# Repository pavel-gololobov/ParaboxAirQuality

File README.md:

# ParaboxAirQuality
CC2538 based board for Parabox.org project

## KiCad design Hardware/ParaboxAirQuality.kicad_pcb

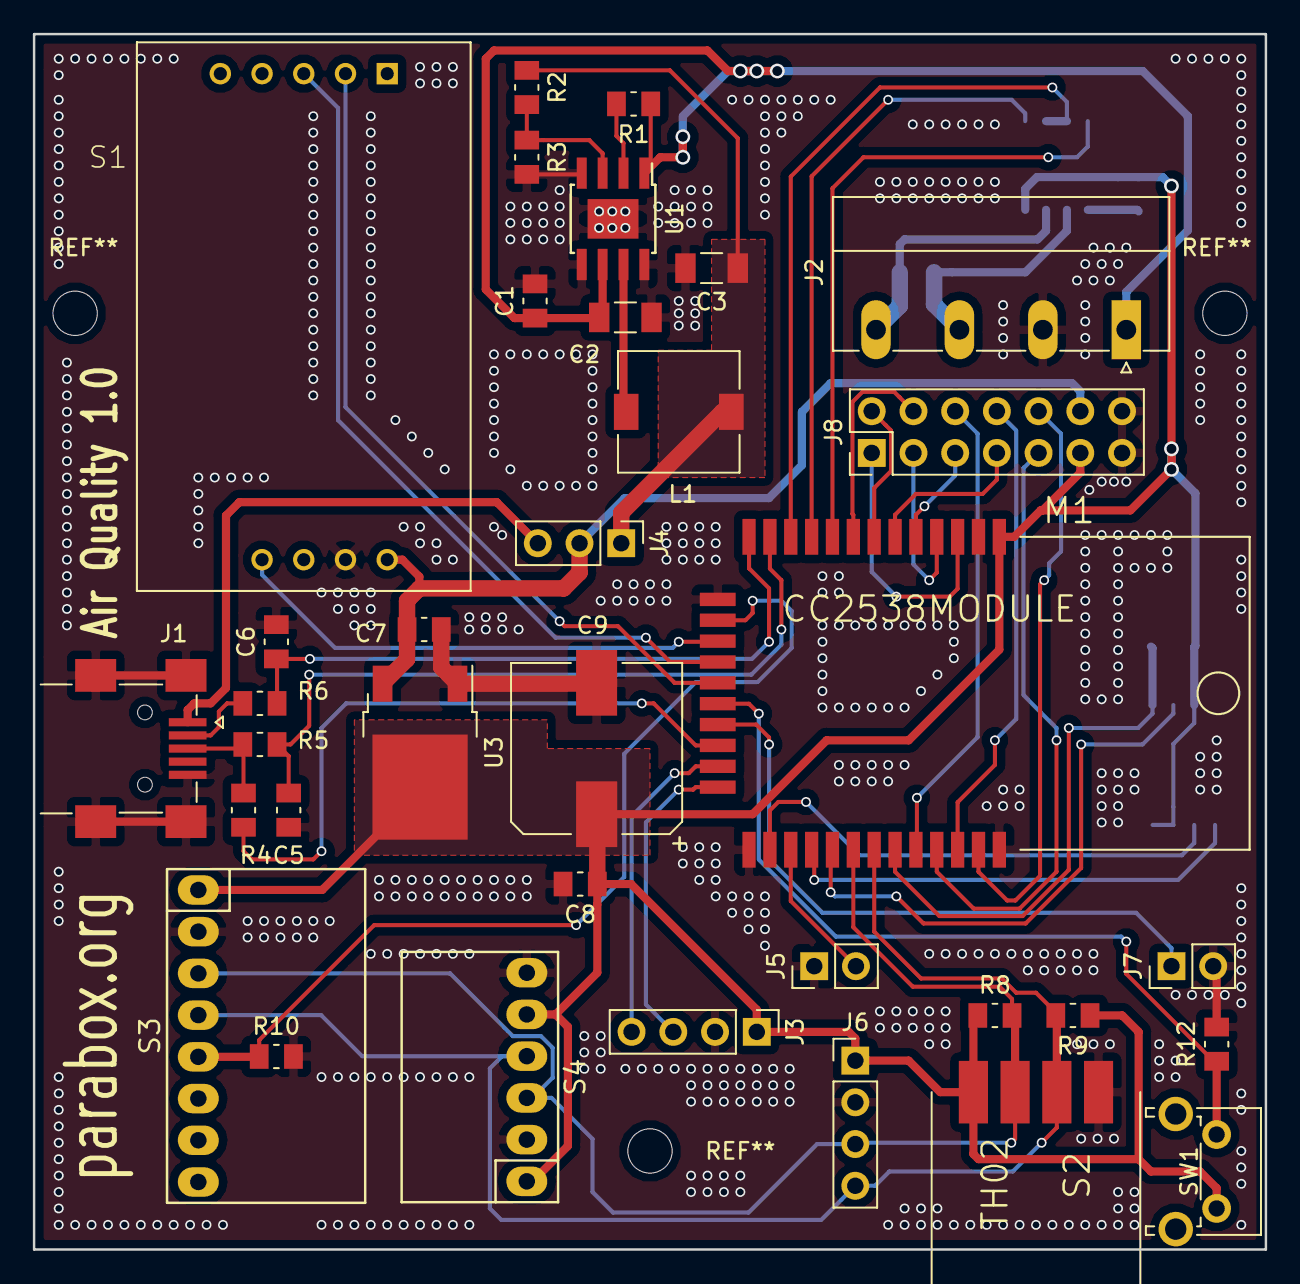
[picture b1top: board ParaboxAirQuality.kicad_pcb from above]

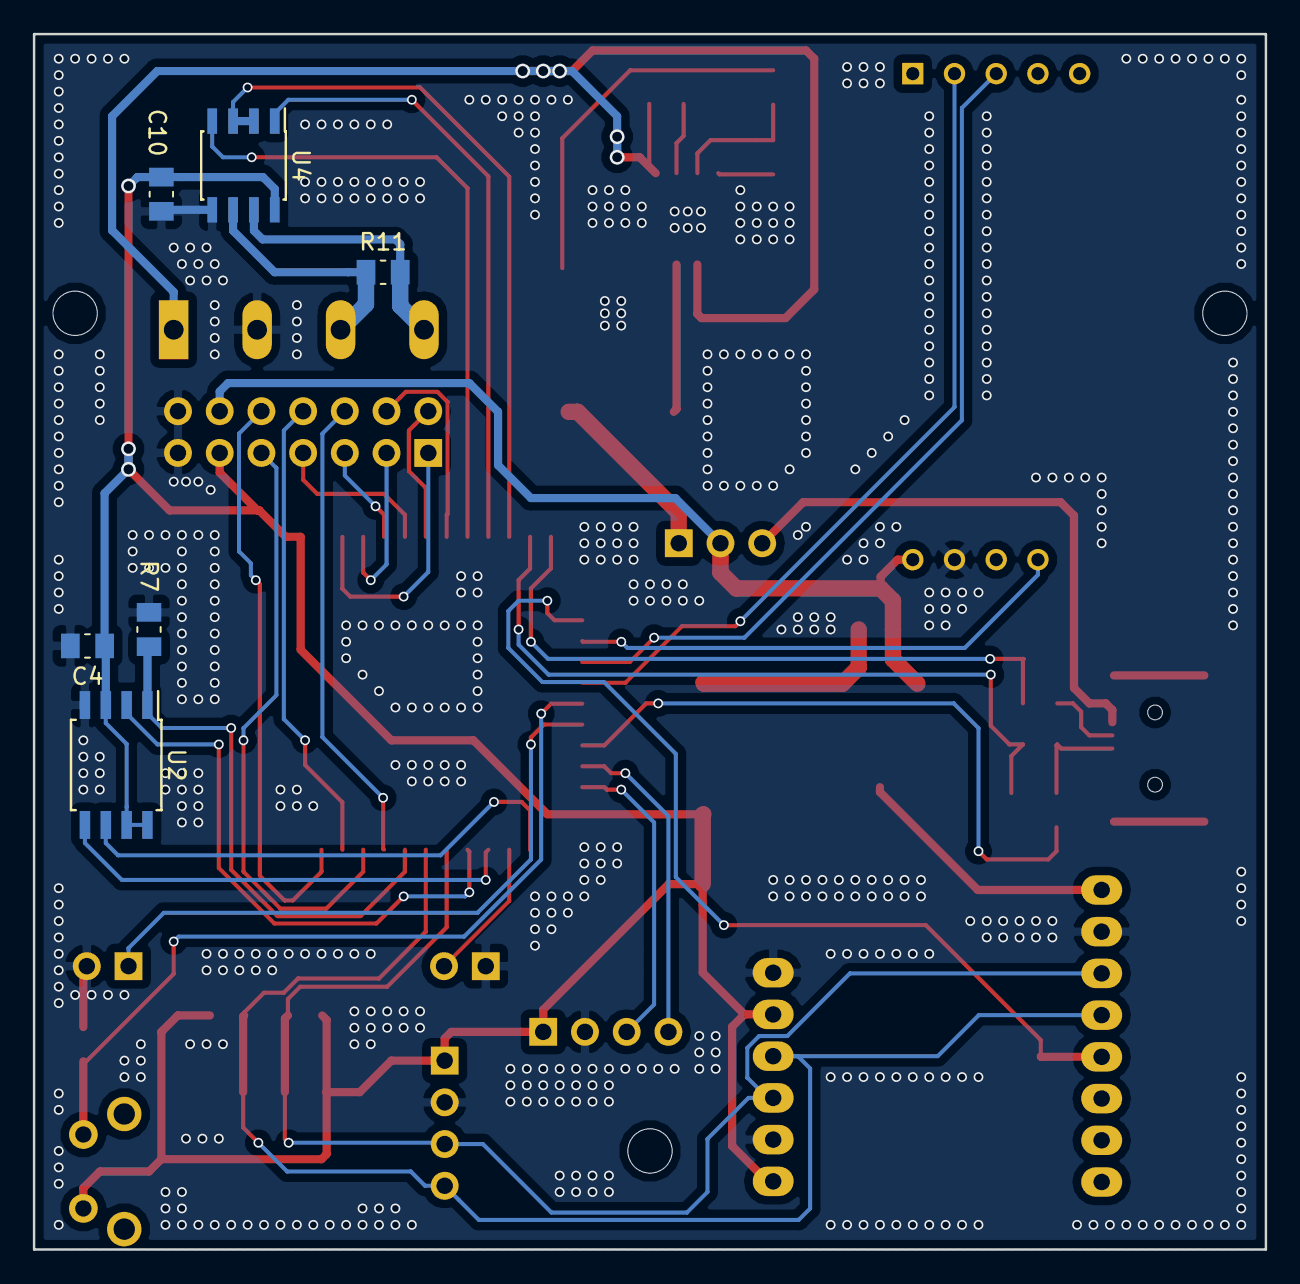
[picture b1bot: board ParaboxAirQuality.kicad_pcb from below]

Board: 2 copper layers, 75.0 x 74.0 mm, 41 parts (6 on the bottom side), 44 nets.

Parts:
C1, C4, C7, C8, C10: 0.1u; C_0805_2012Metric_Pad1.15x1.50mm_HandSolder
C2: 10u; C_1206_3216Metric_Pad1.24x1.80mm_HandSolder
C3: 22u; C_1206_3216Metric_Pad1.24x1.80mm_HandSolder
C5, C6: 47p; C_0805_2012Metric_Pad1.15x1.50mm_HandSolder
C9: CP; CP_Elec_10x10
J1: USB_B_Mini; USB_Mini-B_Lumber_2486_Horizontal
J2: VIN; PhoenixContact_MC_1,5_4-G-5.08_1x04_P5.08mm_Horizontal
J3: BOOT; PinHeader_1x04_P2.54mm_Vertical
J4: Conn_01x03; PinHeader_1x03_P2.54mm_Vertical
J5: BOOT; PinHeader_1x02_P2.54mm_Vertical
J6: I2C; PinHeader_1x04_P2.54mm_Vertical
J7: BEEP; PinHeader_1x02_P2.54mm_Vertical
J8: MISC; PinHeader_2x07_P2.54mm_Vertical
L1: 3R0; L_7.3x7.3_H4.5
M1: CC2538MODULE; CC2538MOD
R1, R7, R8, R9, R10, R12: 10k; R_0805_2012Metric_Pad1.15x1.50mm_HandSolder
R2: 105k; R_0805_2012Metric_Pad1.15x1.50mm_HandSolder
R3: 20k; R_0805_2012Metric_Pad1.15x1.50mm_HandSolder
R4: 1.5k; R_0805_2012Metric_Pad1.15x1.50mm_HandSolder
R5, R6: 33; R_0805_2012Metric_Pad1.15x1.50mm_HandSolder
R11: 120; R_0805_2012Metric_Pad1.15x1.50mm_HandSolder
S1: MH-Z19
S2: TH02; TH02MOD
S3: CJMCU-811
S4: BMP280MOD
SW1: SW_Push; SW_Tactile_SPST_Angled_PTS645Vx83-2LFS
U1: ST1S10PHR; TI_SO-PowerPAD-8
U2: M25PX32-VMW; SOIJ-8_5.3x5.3mm_P1.27mm
U3: LM1117-3.3; TO-252-2
U4: MAX3072E; SOIC-8_3.9x4.9mm_P1.27mm

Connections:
+3V3: C4.1, C8.1, C9.1, C10.1, J3.1, J6.1, J8.11, M1.1, R8.1, R9.1, S2.4, S3.1, S4.1, S4.5, SW1.2, U2.3, U2.7, U2.8, U3.2, U4.8
+5V: C7.1, J4.2, J8.12, S1.6, U3.3
/BEEP: J7.1, M1.20
/BOOT: J5.2, M1.26
/CCS811_WAK: M1.15, R10.1, S3.5
/CO2_PWM: M1.16, S1.9
/I2C_SCK: J6.3, M1.29, R8.2, S2.3, S3.3, S4.3
/I2C_SDA: J6.4, M1.30, R9.2, S2.2, S3.4, S4.4
/JOIN_BUT: M1.19, R12.1, SW1.1
/PB4: J8.4, M1.8
/PB5: J8.2, M1.7
/PD1: J8.6, M1.32
/PD3: J8.8, M1.34
/PD4: J8.10, M1.35
/RESET: J8.9, M1.33
/RS485_A: J2.3, R11.1, U4.6
/RS485_B: J2.4, R11.2, U4.7
/RS485_RE-DE: M1.11, U4.2, U4.3
/SPI_CLK: M1.25, U2.6
/SPI_FLASH_CS: M1.31, R7.1, U2.1
/SPI_RX_MISO: M1.28, U2.2
/SPI_TX_MOSI: M1.27, U2.5
/TCK: J8.3, M1.4
/TDI/PB6: J8.7, M1.6
/TDO/PB7: J8.5, M1.5
/TMS: J8.1, M1.3
/UART0_BOOT_RX: J3.4, M1.22
/UART0_BOOT_TX: J3.3, M1.23
/UART0_RX: M1.17, S1.3
/UART0_TX: M1.18, S1.2
/UART1_RX: M1.9, U4.4
/UART1_TX: M1.10, U4.1
/USB_5V: J1.1, J4.3
/USB_N: C6.1, M1.13, R6.2
/USB_P: C5.1, M1.12, R5.2
/USB_PULL: M1.21, R4.1
/Vin_5V: C3.1, J4.1, L1.2, R2.1
GND: C1.2, C2.2, C3.2, C4.2, C5.2, C6.2, C7.2, C8.2, C9.2, C10.2, J1.5, J1.6, J2.2, J3.2, J5.1, J6.2, J7.2, J8.13, J8.14, M1.2, M1.14, M1.24, M1.36, R3.2, R7.2, R10.2, R12.2, S1.7, S2.1, S3.2, S4.2, S4.6, U1.4, U1.5, U1.8, U1.9, U2.4, U3.1, U4.5
unnamed: J1.2, R6.1
unnamed: J1.3, R4.2, R5.1
unnamed: L1.1, U1.7
unnamed: R1.2, U1.2
unnamed: R2.2, R3.1, U1.3
VCC: C1.1, C2.1, J2.1, R1.1, U1.1, U1.6

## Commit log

2018-03-04 work in progress
2018-03-04 rename libs
2018-03-25 add 485, small fixes
2018-04-01 Final release 1.0, add gerbers
